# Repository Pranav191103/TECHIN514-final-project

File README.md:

# Wireless Temperature Gauge

## Slide 1 — Overview
Wireless Temperature Gauge is a two-device system. A sensor device measures temperature and transmits the value wirelessly. A display device visualizes the temperature using a stepper-motor-driven gauge needle and an LED indicator.

**General sketch:**

---

## Slide 2 — Sensor Device
**Parts:**
- Processor/Wireless: ESP32-C3 (Espressif ESP32-C3-WROOM-02)
- Sensor: Temperature sensor (DS18B20)
- Indicator: LED
- Power: USB

**Operation:**
The ESP32-C3 reads temperature data from the sensor and transmits the measured value wirelessly to the display device.

**Detailed sensor sketch:**

---

## Slide 3 — Display Device
**Parts:**
- Processor/Wireless: ESP32-C3 (Espressif ESP32-C3-WROOM-02)
- Stepper motor: 28BYJ-48 (5V)
- Stepper driver: ULN2003A
- Indicator: LED
- Button: Reset button
- Power: USB

**Operation:**
The display ESP32-C3 receives temperature data, maps the value to a gauge angle, and drives the stepper motor to move the needle. The LED provides visual feedback, and the reset button resets the displayed value.

**Detailed display sketch:**

---

## Slide 4 — Communication & System Diagram
**Communication:**
Sensor ESP32-C3 → Wireless (ESP-NOW or Wi-Fi) → Display ESP32-C3

**System logic:**
Temperature → Measure → Filter → Transmit → Receive → Map to angle → Drive stepper → Update LED

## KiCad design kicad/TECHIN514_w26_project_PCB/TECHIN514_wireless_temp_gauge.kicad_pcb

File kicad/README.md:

KiCad schematic files for sensor device

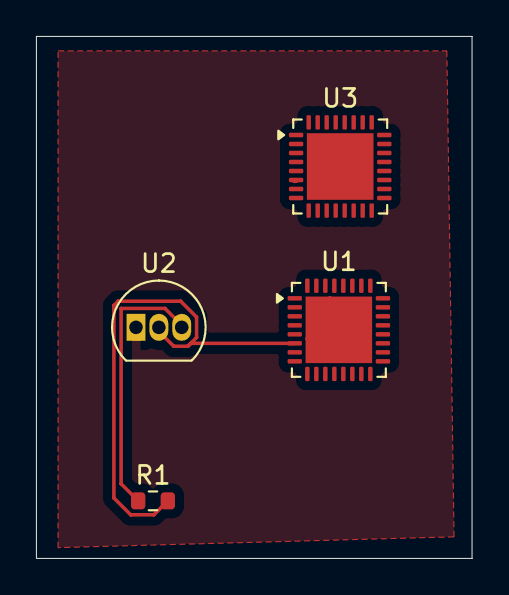
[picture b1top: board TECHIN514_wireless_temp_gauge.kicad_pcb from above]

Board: 2 copper layers, 24.2 x 29.0 mm, 4 parts (0 on the bottom side), 3 nets.

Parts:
R1: R; R_0603_1608Metric
U1: ESP32-C3; QFN-32-1EP_5x5mm_P0.5mm_EP3.7x3.7mm
U2: DS18B20; TO-92_Inline
U3: Seeed Studio XIAO ESP32-C3 (logical representatio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; QFN-32-1EP_5x5mm_P0.5mm_EP3.7x3.7mm

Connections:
+3V3: R1.1, U2.3 (V_{DD}), U3.2 (VDD3P3), U3.3 (VDD3P3)
GND: U1.33 (GND), U2.1 (GND), U3.33 (GND)
unnamed: R1.2, U1.6 (GPIO2), U2.2 (DQ)

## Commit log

2026-01-16 Create datasheets folder
2026-01-16 Create diagrams folder
2026-01-16 Add hardware datasheets
2026-01-16 Add final project milestone README
2026-01-16 Add project diagrams
2026-01-16 Modify operation description in README
    Updated operation description to reflect temperature data reading.
2026-01-16 Align README with temperature-based final project
2026-01-25 Update sensor information in README
2026-01-25 Overview
2026-01-25 senor.png
2026-01-25 display.png
2026-01-25 comm.png
2026-01-25 system.png
2026-01-26 Add README for KiCad schematic files
2026-01-26 Clarify ESP32-C3 description in README
    Updated the ESP32-C3 description for clarity.
2026-01-27 Finalize sensor and display KiCad schematics
2026-01-29 Create TECHIN514_w26_project_PCB
2026-01-29 Fix Lab3 PCB folder and add KiCad schematic files
2026-01-30 Add PCB layout file
2026-01-30 Create screenshots
2026-01-30 Screenshots
2026-01-30 Sensor Device Schematic
2026-01-30 display schematic
